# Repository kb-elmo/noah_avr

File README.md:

# Noah AVR

[![CC BY-NC-SA 4.0][cc-by-nc-sa-shield]][cc-by-nc-sa]

## This project is completed and will not get updated anymore.

### Atmega32u4 based drop-in replacement PCB for the Matrix Noah keyboard

---

[LCSC BOM](noah.csv)

[JLC CPL](noah-bottom-pos.csv)

[JST connectors for USB and RGB](https://www.digikey.de/product-detail/en/jst-sales-america-inc/SM04B-SRSS-TB-LF-SN/455-1804-1-ND/926875)

[SMD standoffs for daughterboard](https://www.digikey.de/en/products/detail/w%C3%BCrth-elektronik/9774030243R/5320628)

---

This work is licensed under a
[Creative Commons Attribution-NonCommercial-ShareAlike 4.0 International License][cc-by-nc-sa].

[![CC BY-NC-SA 4.0][cc-by-nc-sa-image]][cc-by-nc-sa]

[cc-by-nc-sa]: http://creativecommons.org/licenses/by-nc-sa/4.0/
[cc-by-nc-sa-image]: https://licensebuttons.net/l/by-nc-sa/4.0/88x31.png
[cc-by-nc-sa-shield]: https://img.shields.io/badge/License-CC%20BY--NC--SA%204.0-lightgrey.svg

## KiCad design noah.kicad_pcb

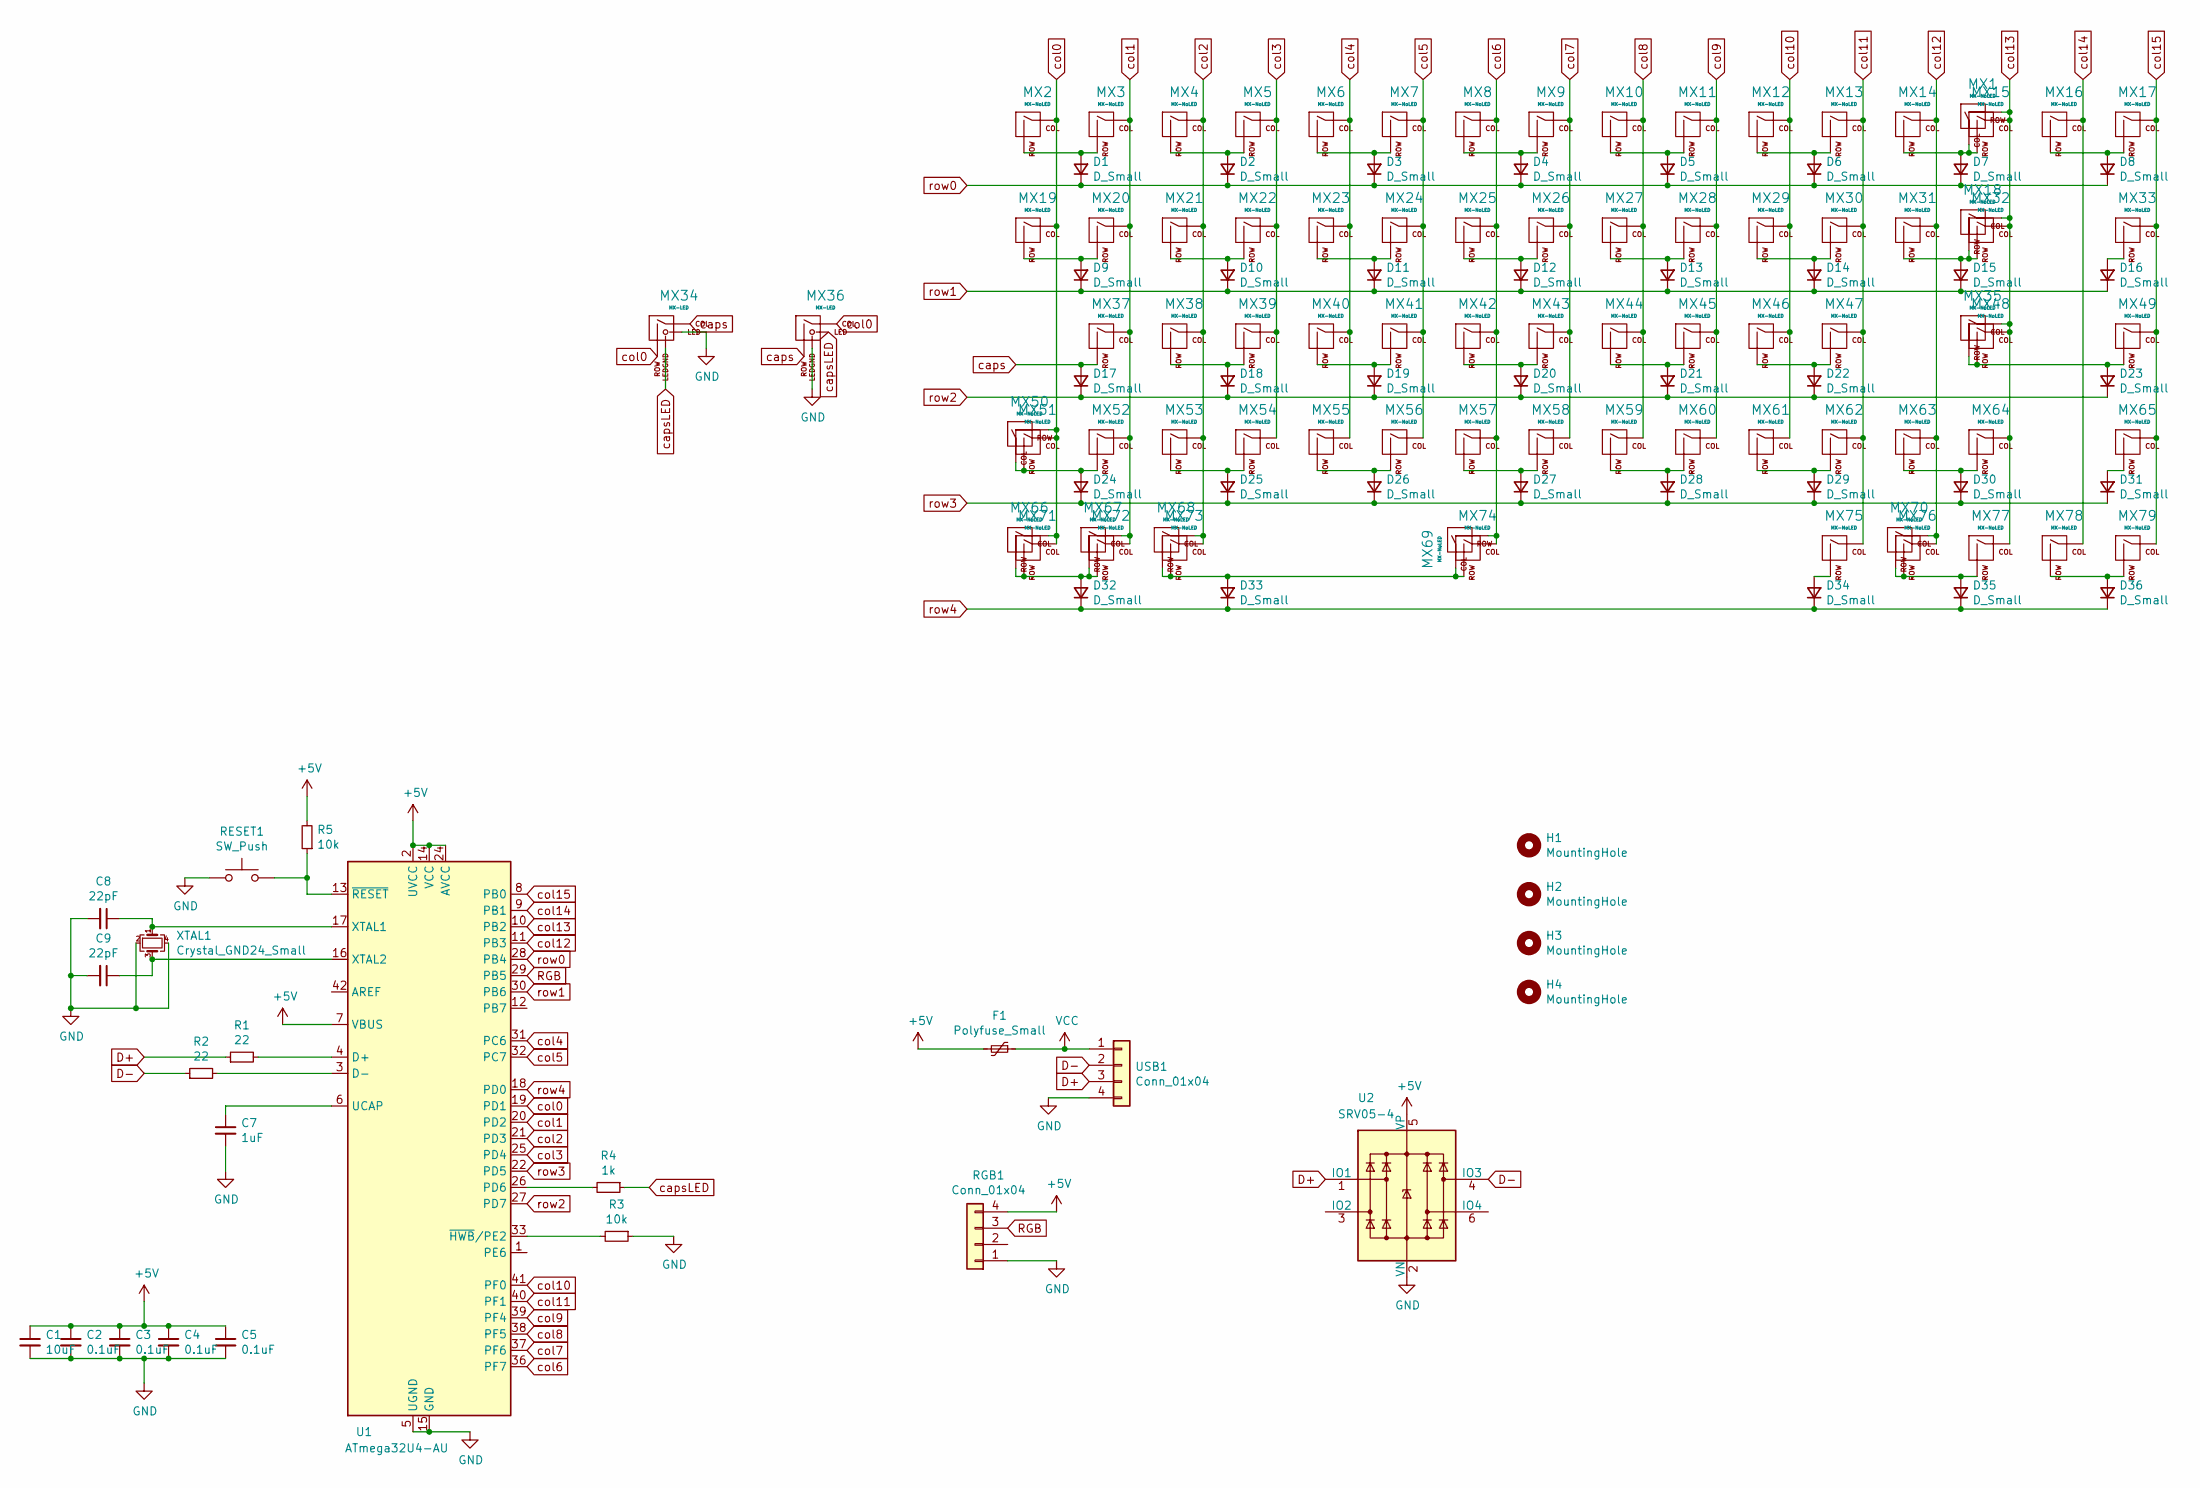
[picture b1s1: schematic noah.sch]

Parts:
C1: 10uF; C_0805_2012Metric; LCSC C91245
C2, C3, C4, C5: 0.1uF; C_0805_2012Metric; LCSC C49678
C7: 1uF; C_0805_2012Metric; LCSC C28323
C8, C9: 22pF; C_0805_2012Metric; LCSC C1804
D1, D2, D3, D4, D5, D6, D7, D8, D9, D10, D11, D12, D13, D14, D15, D17, D18, D19, D20, D21, D22, D23, D24, D25, D26, D27, D28, D29, D30, D32, D33, D35, D36: D_Small; D_SOT-23_ANK; LCSC C68978
D16, D31, D34: D_Small; D_SOD-123; LCSC C81598
F1: Polyfuse_Small; Fuse_1206_3216Metric; LCSC C163133
H1, H2, H3, H4: MountingHole; MountingHole_3mm_Pad_Via
MX1: MX-NoLED; MXOnly-2U-NoLED
MX2, MX3, MX4, MX5, MX6, MX7, MX8, MX9, MX10, MX11, MX12, MX13, MX14, MX15, MX16, MX17, MX18, MX20, MX21, MX22, MX23, MX24, MX25, MX26, MX27, MX28, MX29, MX30, MX31, MX33, MX37, MX38, MX39, MX40, MX41, MX42, MX43, MX44, MX45, MX46, MX47, MX49, MX52, MX53, MX54, MX55, MX56, MX57, MX58, MX59, MX60, MX61, MX62, MX64, MX65, MX67, MX77, MX78, MX79: MX-NoLED; MXOnly-1U-NoLED
MX19, MX32, MX66, MX68, MX70: MX-NoLED; MXOnly-1.5U-NoLED
MX34: MX-LED; MXOnly-1.25U-flipped-LED
MX35: MX-NoLED; MXOnly-ISO-ReversedStabilizers-NoLED
MX36: MX-LED; MXOnly-1.75U
MX48: MX-NoLED; MXOnly-2.25U-ReversedStabilizers-NoLED
MX50, MX71, MX72, MX73, MX75, MX76: MX-NoLED; MXOnly-1.25U-NoLED
MX51: MX-NoLED; MXOnly-2.25U-NoLED
MX63: MX-NoLED; MXOnly-1.75U-NoLED
MX69: MX-NoLED; MXOnly-7U-ReversedStabilizers-NoLED
MX74: MX-NoLED; MXOnly-6.25U-ReversedStabilizers-NoLED
R1, R2: 22; R_0805_2012Metric; LCSC C17561
R3, R5: 10k; R_0805_2012Metric; LCSC C17414
R4: 1k; R_0805_2012Metric; LCSC C17513
RESET1: SW_Push; SKQG-1155865; LCSC C318884
RGB1: Conn_01x04; JST_SH_SM04B-SRSS-TB_1x04-1MP_P1.00mm_Horizontal
U1: ATmega32U4-AU; TQFP-44_10x10mm_P0.8mm; LCSC C44854
U2: SRV05-4; SOT-23-6; LCSC C85364
USB1: Conn_01x04; JST_SH_SM04B-SRSS-TB_1x04-1MP_P1.00mm_Horizontal
XTAL1: Crystal_GND24_Small; Crystal_SMD_3225-4Pin_3.2x2.5mm; LCSC C13738

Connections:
+5V: C1.1, C2.1, C3.1, C4.1, C5.1, F1.2, R5.2, RGB1.4, U1.2 (UVCC), U1.7 (VBUS), U1.14 (VCC), U1.24 (AVCC), U1.34 (VCC), U1.44 (AVCC), U2.5 (VP)
D+: R1.1, U2.1 (IO1), USB1.3
D-: R2.1, U2.4 (IO3), USB1.2
GND: C1.2, C2.2, C3.2, C4.2, C5.2, C7.2, C8.2, C9.2, MX34.3 (LED), MX36.4 (LEDGND), R3.1, RESET1.1, RGB1.1, U1.5 (UGND), U1.15 (GND), U1.23 (GND), U1.35 (GND), U1.43 (GND), U2.2 (VN), USB1.4, XTAL1.2, XTAL1.4; also elsewhere on the board
unnamed: C7.1, U1.6 (UCAP)
unnamed: C8.1, U1.17 (XTAL1), XTAL1.1
unnamed: C9.1, U1.16 (XTAL2), XTAL1.3
unnamed: D1.2 (A), MX2.2 (ROW), MX3.2 (ROW)
unnamed: D2.2 (A), MX4.2 (ROW), MX5.2 (ROW)
unnamed: D3.2 (A), MX6.2 (ROW), MX7.2 (ROW)
unnamed: D4.2 (A), MX8.2 (ROW), MX9.2 (ROW)
unnamed: D5.2 (A), MX10.2 (ROW), MX11.2 (ROW)
unnamed: D6.2 (A), MX12.2 (ROW), MX13.2 (ROW)
unnamed: D7.2 (A), MX1.1 (COL), MX14.2 (ROW), MX15.2 (ROW)
unnamed: D8.2 (A), MX16.2 (ROW), MX17.2 (ROW)
unnamed: D9.2 (A), MX19.2 (ROW), MX20.2 (ROW)
unnamed: D10.2 (A), MX21.2 (ROW), MX22.2 (ROW)
unnamed: D11.2 (A), MX23.2 (ROW), MX24.2 (ROW)
unnamed: D12.2 (A), MX25.2 (ROW), MX26.2 (ROW)
unnamed: D13.2 (A), MX27.2 (ROW), MX28.2 (ROW)
unnamed: D14.2 (A), MX29.2 (ROW), MX30.2 (ROW)
unnamed: D15.2 (A), MX18.2 (ROW), MX31.2 (ROW), MX32.2 (ROW)
unnamed: D16.2 (A), MX33.2 (ROW)
unnamed: D18.2 (A), MX38.2 (ROW), MX39.2 (ROW)
unnamed: D19.2 (A), MX40.2 (ROW), MX41.2 (ROW)
unnamed: D20.2 (A), MX42.2 (ROW), MX43.2 (ROW)
unnamed: D21.2 (A), MX44.2 (ROW), MX45.2 (ROW)
unnamed: D22.2 (A), MX46.2 (ROW), MX47.2 (ROW)
unnamed: D23.2 (A), MX35.2 (ROW), MX48.2 (ROW), MX49.2 (ROW)
unnamed: D24.2 (A), MX50.1 (COL), MX51.2 (ROW), MX52.2 (ROW)
unnamed: D25.2 (A), MX53.2 (ROW), MX54.2 (ROW)
unnamed: D26.2 (A), MX55.2 (ROW), MX56.2 (ROW)
unnamed: D27.2 (A), MX57.2 (ROW), MX58.2 (ROW)
unnamed: D28.2 (A), MX59.2 (ROW), MX60.2 (ROW)
unnamed: D29.2 (A), MX61.2 (ROW), MX62.2 (ROW)
unnamed: D30.2 (A), MX63.2 (ROW), MX64.2 (ROW)
unnamed: D31.2 (A), MX65.2 (ROW)
unnamed: D32.2 (A), MX66.2 (ROW), MX67.2 (ROW), MX71.2 (ROW), MX72.2 (ROW)
unnamed: D33.2 (A), MX68.2 (ROW), MX69.1 (COL), MX73.2 (ROW), MX74.2 (ROW)
unnamed: D34.2 (A), MX75.2 (ROW)
unnamed: D35.2 (A), MX70.2 (ROW), MX76.2 (ROW), MX77.2 (ROW)
unnamed: D36.2 (A), MX78.2 (ROW), MX79.2 (ROW)
unnamed: R1.2, U1.4 (D+)
unnamed: R2.2, U1.3 (D-)
unnamed: R3.2, U1.33 (~HWB~/PE2)
unnamed: R4.2, U1.26 (PD6)
unnamed 46: R5.1, RESET1.2, U1.13 (~RESET); also elsewhere on the board
RGB: RGB1.3, U1.29 (PB5)
VCC: F1.1, USB1.1
caps: D17.2 (A), MX34.1 (COL), MX36.2 (ROW), MX37.2 (ROW)
capsLED: MX34.4 (LEDGND), MX36.3 (LED), R4.1
col0: MX2.1 (COL), MX19.1 (COL), MX34.2 (ROW), MX36.1 (COL), MX50.2 (ROW), MX51.1 (COL), MX66.1 (COL), MX71.1 (COL), U1.19 (PD1)
col1: MX3.1 (COL), MX20.1 (COL), MX37.1 (COL), MX52.1 (COL), MX67.1 (COL), MX72.1 (COL), U1.20 (PD2)
col2: MX4.1 (COL), MX21.1 (COL), MX38.1 (COL), MX53.1 (COL), MX68.1 (COL), MX73.1 (COL), U1.21 (PD3)
col3: MX5.1 (COL), MX22.1 (COL), MX39.1 (COL), MX54.1 (COL), U1.25 (PD4)
col4: MX6.1 (COL), MX23.1 (COL), MX40.1 (COL), MX55.1 (COL), U1.31 (PC6)
col5: MX7.1 (COL), MX24.1 (COL), MX41.1 (COL), MX56.1 (COL), U1.32 (PC7)
col6: MX8.1 (COL), MX25.1 (COL), MX42.1 (COL), MX57.1 (COL), MX69.2 (ROW), MX74.1 (COL), U1.36 (PF7)
col7: MX9.1 (COL), MX26.1 (COL), MX43.1 (COL), MX58.1 (COL), U1.37 (PF6)
col8: MX10.1 (COL), MX27.1 (COL), MX44.1 (COL), MX59.1 (COL), U1.38 (PF5)
col9: MX11.1 (COL), MX28.1 (COL), MX45.1 (COL), MX60.1 (COL), U1.39 (PF4)
col10: MX12.1 (COL), MX29.1 (COL), MX46.1 (COL), MX61.1 (COL), U1.41 (PF0)
col11: MX13.1 (COL), MX30.1 (COL), MX47.1 (COL), MX62.1 (COL), MX75.1 (COL), U1.40 (PF1)
col12: MX14.1 (COL), MX31.1 (COL), MX63.1 (COL), MX70.1 (COL), MX76.1 (COL), U1.11 (PB3)
col13: MX1.2 (ROW), MX15.1 (COL), MX18.1 (COL), MX32.1 (COL), MX35.1 (COL), MX48.1 (COL), MX64.1 (COL), MX77.1 (COL), U1.10 (PB2)
col14: MX16.1 (COL), MX78.1 (COL), U1.9 (PB1)
col15: MX17.1 (COL), MX33.1 (COL), MX49.1 (COL), MX65.1 (COL), MX79.1 (COL), U1.8 (PB0)
row0: D1.1 (K), D2.1 (K), D3.1 (K), D4.1 (K), D5.1 (K), D6.1 (K), D7.1 (K), D8.1 (K), U1.28 (PB4)
row1: D9.1 (K), D10.1 (K), D11.1 (K), D12.1 (K), D13.1 (K), D14.1 (K), D15.1 (K), D16.1 (K), U1.30 (PB6)
row2: D17.1 (K), D18.1 (K), D19.1 (K), D20.1 (K), D21.1 (K), D22.1 (K), D23.1 (K), U1.27 (PD7)
row3: D24.1 (K), D25.1 (K), D26.1 (K), D27.1 (K), D28.1 (K), D29.1 (K), D30.1 (K), D31.1 (K), U1.22 (PD5)
row4: D32.1 (K), D33.1 (K), D34.1 (K), D35.1 (K), D36.1 (K), U1.18 (PD0)

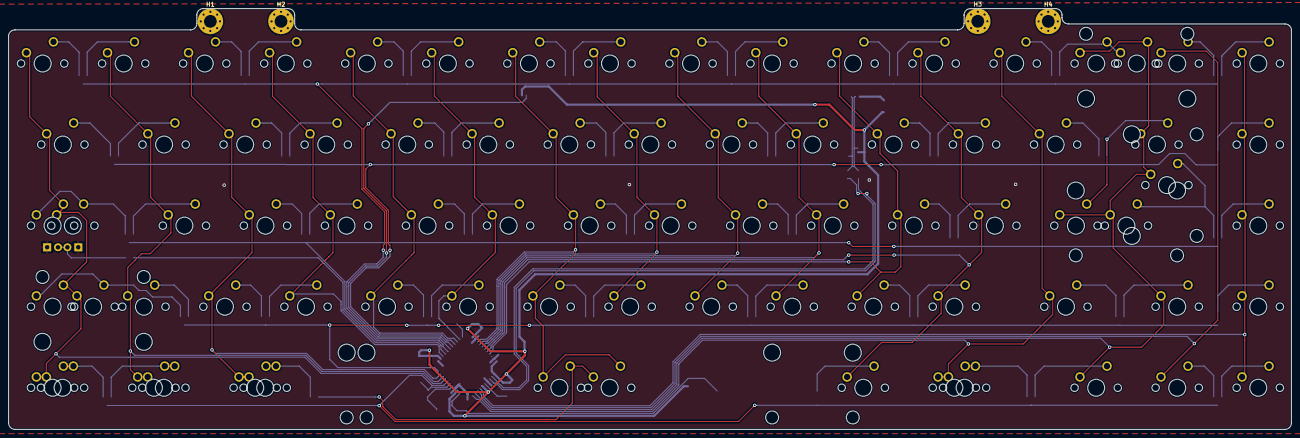
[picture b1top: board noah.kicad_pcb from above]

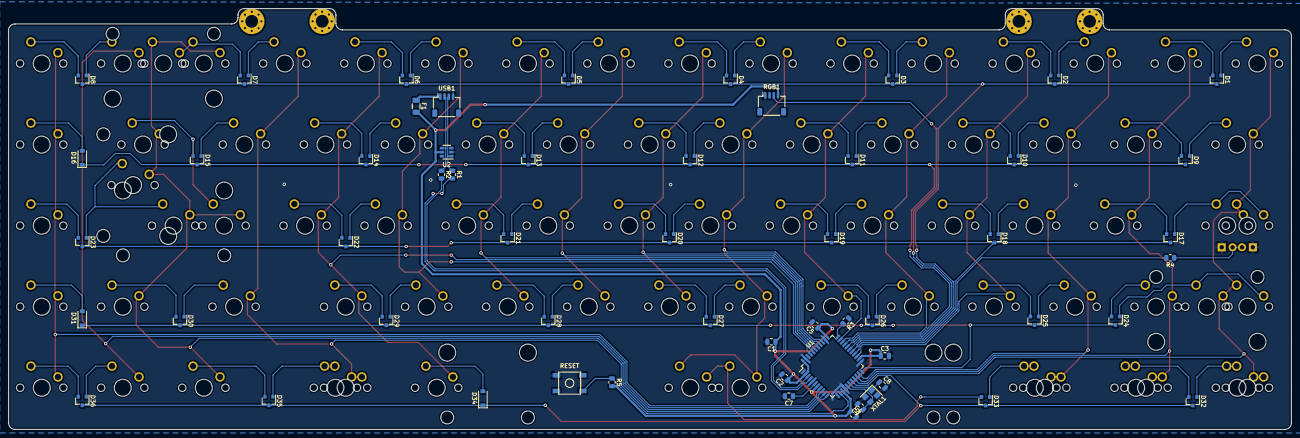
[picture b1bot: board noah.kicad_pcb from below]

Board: 2 copper layers, 301.5 x 98.9 mm, 139 parts (56 on the bottom side), 72 nets.

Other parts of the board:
RESET: SW_Push; SKQG-1155865

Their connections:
GND: RESET.1; also elsewhere on the board
unnamed 46: RESET.2; also elsewhere on the board

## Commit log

2021-01-02 add LCSC BOM and placing files
2021-01-02 cleanup
2021-01-02 fix BOM
2021-01-03 update BOM
2021-01-04 Create LICENSE
2021-01-14 fix DB plug wire orientation
2021-01-14 update gerbers
